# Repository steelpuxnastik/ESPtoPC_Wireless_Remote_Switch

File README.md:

# ESPtoPC Wireless Remote Switch

Remote power-on / reset / force-shutdown for a desktop PC over WiFi, using an ESP-01 wired to the motherboard's front-panel header, plus an OpenWrt app (LuCI page + CLI) to manage one or more of these boards.

Built for the case where a PC needs to be turned on remotely even after a power outage — before the OS is up, before Wake-on-LAN is usable — by literally pressing the physical power button in software.

## Repo layout

```
├── esptopc_poweron_remote_pcb/
│   ├── esptopc_poweron_remote_pcb.kicad_pro   KiCad project
│   ├── esptopc_poweron_remote_pcb.kicad_pcb   Board layout
│   ├── esptopc_poweron_remote_pcb.kicad_sch   Schematic
│   └── esptopc_poweron_remote_pcb.kicad_prl   KiCad local project settings
├── esptopc_poweron_remote/
│   └── esptopc_poweron_remote.ino             ESP8266 (ESP-01) firmware
└── openwrt_program/
    └── deploy.sh                              One-shot installer for the OpenWrt side:
                                               LuCI app + CLI tool + handshake listener
```

## How it fits together

```
[ESP-01 board]  --HTTP-->  [OpenWrt router]  <--LuCI/SSH--  [you]
   |    ^                     |
   |    |                     |-- LuCI page: device list, status, buttons
   |    `-- commands sent      -- CLI (`esptopcrsw`): menu + one-liners
   |        by OpenWrt         -- receives handshake/heartbeat from ESP
   `-- wired to PC's
       PWR_SW / RESET_SW
       header + reads the
       power-LED line
```

- The ESP-01 runs its own tiny HTTP server (power on / force off / reset / status) and also announces itself to the router (MAC + a fixed identifying string) so it shows up in LuCI ready to be named and saved.
- The OpenWrt side is the "brain": it tracks device state, decides which buttons make sense to show (e.g. no point offering "Reset" on a PC that's already off), and is what you actually interact with — LuCI in a browser, or `esptopcrsw` over SSH.

## Hardware (KiCad project)

Open `esptopc_poweron_remote_pcb.kicad_pro` in KiCad. The board:

- Regulates the PC's 5V standby rail down to 3.3V (AMS1117-3.3) to power the ESP-01;
- Uses two small MOSFET pairs (PMOS+NMOS per line) so the ESP's GPIO1 (TX) and GPIO3 (RX) can pull the motherboard's **PWR_SW** and **RESET_SW** header pins low, exactly like pressing the physical buttons;
- Reads the motherboard's power-LED line through a third MOSFET into GPIO2, to sense whether the PC is currently on (active-low: LOW = on);
- Leaves GPIO0 completely unused/unconnected on purpose, to avoid accidentally dropping into the bootloader.

### List of required components for board assembly

| Reference | Qty | Value | Footprint | Datasheet |
| :--- | :--- | :--- | :--- | :--- |
| **C1** | 1 | 22uF | Capacitor_Tantalum_SMD:CP_EIA-3528-21_Kemet-B_HandSolder | |
| **C2** | 1 | 150uF | Capacitor_Tantalum_SMD:CP_EIA-6032-28_Kemet-C_HandSolder | |
| **C3** | 1 | 100nF | Capacitor_SMD:C_1206_3216Metric_Pad1.33x1.80mm_HandSolder | |
| **C4** | 1 | 1uF | Capacitor_SMD:C_0805_2012Metric_Pad1.18x1.45mm_HandSolder | |
| **J1** | 1 | Conn_01x05_Pin | Connector_PinHeader_2.54mm:PinHeader_1x05_P2.54mm_Vertical | |
| **Q1, Q3** | 2 | IRLML6402 | Package_TO_SOT_SMD:SOT-23_Handsoldering | |
| **Q2, Q4, Q5** | 3 | IRLML2502 | Package_TO_SOT_SMD:SOT-23_Handsoldering | |
| **R1, R2, R3, R4, R5, R6, R8, R9** | 8 | 10k | Resistor_SMD:R_1206_3216Metric_Pad1.30x1.75mm_HandSolder | |
| **R7** | 1 | 1k | Resistor_SMD:R_0805_2012Metric | |
| **U1** | 1 | AMS1117-3.3 (fixed 3.3V version) | Package_TO_SOT_SMD:SOT-223-3_TabPin2 | [Datasheet](http://www.advanced-monolithic.com/pdf/ds1117.pdf) |
| **U2** | 1 | ESP-01 | RF_Module:ESP-01 | [Datasheet](https://aithinker-static.oss-cn-shenzhen.aliyuncs.com/docs/_media_old/esp-01_product_specification_en.pdf) |

## Connection to PC

Connector `J1` (5-pin) goes to the motherboard. Pinout as drawn in the schematic:

| J1 pin | Signal | Connect to |
| :--- | :--- | :--- |
| 1 | LED+ | Power-LED (PLED+) pin of the motherboard's front-panel header |
| 2 | RESET | Signal pin of the RESET_SW header (not the ground pin) |
| 3 | POWER | Signal pin of the PWR_SW header (not the ground pin) |
| 4 | GND | Ground |
| 5 | +5V | +5V standby — must stay powered while the PC is off |

Front-panel header pinouts differ between motherboards, so check the manual of yours before connecting.

## Firmware (`esptopc_poweron_remote.ino`)

Flash with the Arduino IDE (ESP8266 core) via a USB-serial adapter. **TX/RX are used to drive the buttons**, so there's no Serial debug output. Flashing needs the special adapter, so you need to disconnect ESP-01 from the board first.

Before flashing, edit near the top of the file:

- `WIFI_SSID` / `WIFI_PASS` — your network;
- `DEVICE_PASSWORD` — a shared password string. The board sends it to the router in the handshake (so the router knows it's one of yours), and it is also the seed of the per-device command key (see **Security** below). It must match `esptopcrsw.settings.password` on the router; the default `poweron-esp01` is already the same on both sides, so you don't have to change it;
- `POWER_SHORT_MS = 300` - A short press of the Power button. The configured press duration setting should work in most cases;
- `POWER_SOFTOFF_MS  = 4500` - Hold the Power button for the BIOS "soft-off delay" (e.g. Gigabyte: *Soft-Off by PWR-BTN = Delay 4 Sec*: a short press only suspends the PC, holding the button for 4+ seconds turns it off). It is only a fallback: the router normally sends its own time, see **Button press times** below;
- `POWER_FORCEOFF_MS = 5000` - Long-press the Power button to force the system unit to shut down. The required duration of the press can vary significantly between different computers; if it does not work, you will need to experiment to find the right timing;
- `RESET_SHORT_MS = 300` - A short press of the Reset button. The configured press duration setting should work in most cases;
- `WIFI_RETRY_MS = 30000` - While the board is not connected to WiFi (for example, the router is still booting after a power outage), it retries the connection every 30 seconds, forever;
- `HANDSHAKE_INTERVAL_MS = 10000` - Once the board is on WiFi, until the OpenWrt app acknowledges it, it announces itself every 10 seconds;
- `HEARTBEAT_INTERVAL_MS = 90000` - After the acknowledgment the board repeats the announcement every 90 seconds to show it is still alive.

How the heartbeat is used: the router stores the time of the last announcement in RAM, continuously, whether or not anyone has the LuCI page open. A device is shown as Offline if nothing was heard from it for 5 minutes. The PC's on/off state does not come from the heartbeat — it is read live from the board when you open the page (and every 15 seconds while the page stays open). The only case with a wait is right after the router itself reboots: its RAM is empty, so a device shows as Offline until its next announcement (up to the heartbeat interval). A shorter `HEARTBEAT_INTERVAL_MS` shortens that wait.

The board finds the router automatically (`WiFi.gatewayIP()`, no IP to hardcode) and keeps retrying forever, so boot order after a power outage doesn't matter.

HTTP endpoints the board exposes (all require `?key=...`, see below):

| Endpoint         | Effect                        |
|-------------------|-------------------------------|
| `GET /power/on[?ms=N]`   | Short press of the power button (default `POWER_SHORT_MS`; limited to 100–2000) |
| `GET /power/hold[?ms=N]` | Hold the power button (default `POWER_SOFTOFF_MS`; limited to 500–10000) |
| `GET /power/off[?ms=N]`  | Long press, force shutdown (default `POWER_FORCEOFF_MS`; limited to 1000–15000) |
| `GET /reset[?ms=N]`      | Press of the reset button (default `RESET_SHORT_MS`; limited to 100–2000) |
| `GET /status`     | `{"pc_status":"on"\|"off"}`   |

All permission logic (e.g. "don't offer Reset while the PC is off") lives on the OpenWrt side, not in the firmware — the board just does what it's told and reports state.

## OpenWrt app (`deploy.sh`)

Self-contained installer — no package manager involved, just copies files to their real system paths and (re)starts the relevant services. Built against OpenWrt 25.x (APK-based, modern JSON-based LuCI menu/ACL — the classic Lua-controller style LuCI apps won't work the same way on this version).

### Install

On Windows, in CMD, I use this to copy `deploy.sh` to the router:
```CMD
scp X:\way\to\your\deploy.sh root@<router-ip>:/root/
```
After this, connect to the router over SSH and install the app:
```sh
ssh root@<router-ip>
sh deploy.sh
```

Re-running `deploy.sh` after an update is safe — it won't wipe devices you've already added (`/etc/config/esptopcrsw` is only created if missing).

What it sets up:
- LuCI page under **Services → ESPtoPC Wireless Remote Switch**: device table with live status (On / Off / Offline), buttons that adapt to state, add-device picker (from the router's DHCP client list or typed by hand), and a banner for boards that announced themselves but aren't saved yet (it has a Dismiss button; a dismissed board shows up again when it announces itself next time). **Initial setup and adding devices is carried out only in LuCI's ESPtoPC Wireless Remote Switch program page**;
- `esptopcrsw` CLI (see below; use it only after the setup in LuCI is done and checked);
- A second `uhttpd` instance on port 8090 that receives the handshake/heartbeat from ESP boards;
- `rpcd`/`ubus` backend (`/usr/libexec/rpcd/esptopcrsw`) that both the LuCI page and the CLI talk to.

### CLI

> **Important:**
> Use the CLI only after the program is set up in LuCI and you have checked that everything works as you expect: devices are added, the status is shown correctly, and the press times (the **Settings** button of each device) fit your PC. The CLI does not add devices or change settings, it only sends commands using what is configured in LuCI.

```sh
esptopcrsw                     # interactive menu, a convenient alternative to manual command entry
esptopcrsw list                # table of devices + status
esptopcrsw poweron <name>      # power on (or sleep, if already on)
esptopcrsw softoff <name>      # soft-off: hold Power for the BIOS delay (see below; `hold` is an alias)
esptopcrsw off <name>          # force power off (long hold)
esptopcrsw reset <name>
esptopcrsw check <name>        # check/restore connection
esptopcrsw help                # show help (list of commands and hints)
esptopcrsw lang [en|ru|uk]     # interface language (remembered)
```

Any of `poweron` / `softoff` / `off` / `reset` asks for a one-letter confirmation first (`y/N`) naming the device and the action, so a stray keypress can't send a command to the wrong PC. If a device looks offline when you run a command, the CLI tries to reconnect first and reports what happened, instead of failing silently.

### Button press times and Soft-Off

**Soft-Off is optional and aimed at Gigabyte boards.** Some Gigabyte BIOSes have *Soft-Off by PWR-BTN* (*Instant-Off* / *Delay 4 Sec*). With *Delay 4 Sec* a short press only suspends the PC, and a press held for 4 seconds shuts it down normally. If your board has no such option, you only need **Off / Sleep** and **Force Off**. The same action also covers any other case where the PC expects a Power press of a specific length: set that length as the hold time.

Power button actions, from shortest to longest: **Off / Sleep** (short press, what the PC does depends on its power settings), **Soft-Off (X s)** (hold for the BIOS soft-off delay), **Force Off** (long hold, `POWER_FORCEOFF_MS`), and **Reset**.

If a short press does not shut the PC down (on Gigabyte boards the BIOS option *Soft-Off by PWR-BTN* set to *Delay 4 Sec* makes a short press only suspend it), use **Soft-Off (X s)**. `X` is set with the **Settings** button in LuCI (in seconds) or on the router, no reflashing needed:

All press times are set per device in LuCI, in seconds, no reflashing needed: the **Settings** button in the device's *Manage* column (an empty field means the built-in value). The same options can be set with `uci` in the device section:

```sh
uci set esptopcrsw.@device[0].soft_off_ms='6000'    # the first device, ms
uci commit esptopcrsw
```

| Option | Action | Default | Allowed, ms |
|---|---|---|---|
| `power_short_ms` | Off / Sleep (short Power press) | 300 | 100–2000 |
| `soft_off_ms` | Soft-Off (Power hold for the BIOS delay) | 4500 | 500–10000 |
| `force_off_ms` | Force Off (long Power hold) | 5000 | 1000–15000 |
| `reset_ms` | Reset | 300 | 100–2000 |

The Soft-Off button label in LuCI and in the CLI shows the current value for that device. Unlike the short press, this button is not blocked in the first minute after power-on.

### Security

There's no login/password on the ESP's HTTP server itself — instead:

- **Handshake** (ESP → router): the board POSTs its MAC and `DEVICE_PASSWORD` to the router on boot/periodically, so the router knows it's genuinely this project's firmware announcing itself. It only filters out random devices, and it is sent in plain text.
- **Commands** (router → ESP): every `/power/on`, `/power/hold`, `/power/off`, `/reset`, `/status` call requires `?key=<12-hex-chars>`, computed as `md5(MAC:DEVICE_PASSWORD)` truncated to 12 characters — the same formula on both sides, so no separate secret needs to be distributed or synced per board. Each board gets a different key because its MAC is different. This stops a stray browser tab pointed at the board's IP from doing anything. It is **not** protection against someone who deliberately reads this repo (the formula and the default password are public), and it's **not encryption**: the key is part of the URL, so anyone sniffing the WiFi traffic can read it in plain text. Good enough for "don't let someone on the LAN poke it by accident", not meant to survive a hostile network. If you want more than the default, set your own string in `DEVICE_PASSWORD` in the firmware and in `uci set esptopcrsw.settings.password='...'` on the router.

## Known rough edges

- The rpcd/JS/LuCI layer was written against documented conventions for modern OpenWrt (menu.d/acl.d JSON, JS views over ubus) but hasn't been exhaustively tested beyond this one setup — if something in LuCI breaks after an OpenWrt upgrade, that's the first place to look.
- `busybox tr` on some builds doesn't support POSIX character classes (`[:lower:]`/`[:upper:]`) — the scripts here use explicit ranges (`a-z`/`A-Z`) everywhere for that reason; keep that in mind if you extend them.
- MAC addresses are stored/compared uppercase throughout, to avoid the same device getting registered twice under different casing.

## To-Do-List
- PCB variant based on ESP12E, that will be simpler in some areas in terms of harnessing components, plus it's protected by default from all the side effects that previously had to be addressed by monitoring the input from the PC's operating status pin. 
- Create a simplified default pass-through connection for all connectors, plus the ability to connect to the power supply with just one 5Vsb wire.

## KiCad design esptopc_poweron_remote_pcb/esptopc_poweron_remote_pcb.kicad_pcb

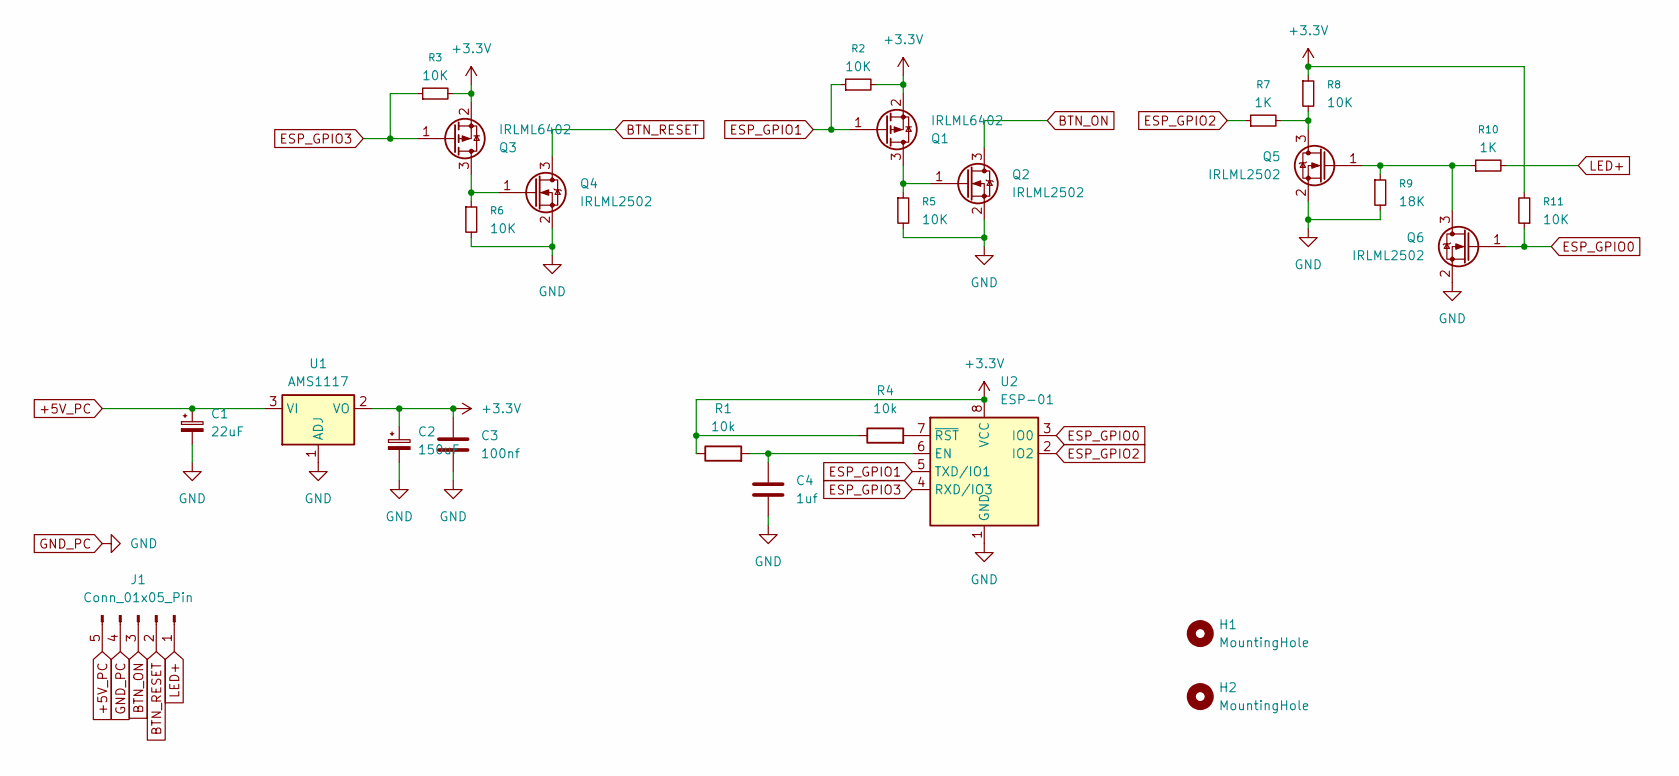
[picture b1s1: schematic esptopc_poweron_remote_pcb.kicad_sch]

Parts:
C1: 22uF; CP_EIA-3528-21_Kemet-B_HandSolder
C2: 150uF; CP_EIA-6032-28_Kemet-C_HandSolder
C3: 100nf; C_1206_3216Metric_Pad1.33x1.80mm_HandSolder
C4: 1uf; C_0805_2012Metric_Pad1.18x1.45mm_HandSolder
H1, H2: MountingHole; MountingHole_3.2mm_M3
J1: Conn_01x05_Pin; PinHeader_1x05_P2.54mm_Vertical
Q1, Q3: IRLML6402; SOT-23_Handsoldering
Q2, Q4, Q5, Q6: IRLML2502; SOT-23_Handsoldering
R1, R4: 10k; R_1206_3216Metric_Pad1.30x1.75mm_HandSolder
R2, R3, R5, R6, R8, R11: 10K; R_1206_3216Metric_Pad1.30x1.75mm_HandSolder
R7: 1K; R_0805_2012Metric
R9: 18K; R_0805_2012Metric_Pad1.20x1.40mm_HandSolder
R10: 1K; R_0805_2012Metric_Pad1.20x1.40mm_HandSolder
U1: AMS1117; SOT-223-3_TabPin2
U2: ESP-01

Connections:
+3.3V: C2.1, C3.1, Q1.2 (S), Q3.2 (S), R1.1, R2.2, R3.2, R4.1, R8.1, R11.2, U1.2 (VO), U2.8 (VCC)
+5V_PC: C1.1, J1.5, U1.3 (VI)
BTN_ON: J1.3, Q2.3 (D)
BTN_RESET: J1.2, Q4.3 (D)
ESP_GPIO0: Q6.1 (G), R11.1, U2.3 (IO0)
ESP_GPIO1: Q1.1 (G), R2.1, U2.5 (TXD/IO1)
ESP_GPIO2: R7.1, U2.2 (IO2)
ESP_GPIO3: Q3.1 (G), R3.1, U2.4 (RXD/IO3)
GND_PC: C1.2, C2.2, C3.2, C4.2, J1.4, Q2.2 (S), Q4.2 (S), Q5.2 (S), Q6.2 (S), R5.2, R6.2, R9.2, U1.1 (ADJ), U2.1 (GND)
LED+: J1.1, R10.2
unnamed: Q1.3 (D), Q2.1 (G), R5.1
unnamed: Q3.3 (D), Q4.1 (G), R6.1
unnamed: Q5.3 (D), R7.2, R8.2
unnamed: Q5.1 (G), Q6.3 (D), R9.1, R10.1
unnamed: C4.1, R1.2, U2.6 (EN)
unnamed: R4.2, U2.7 (~RST)

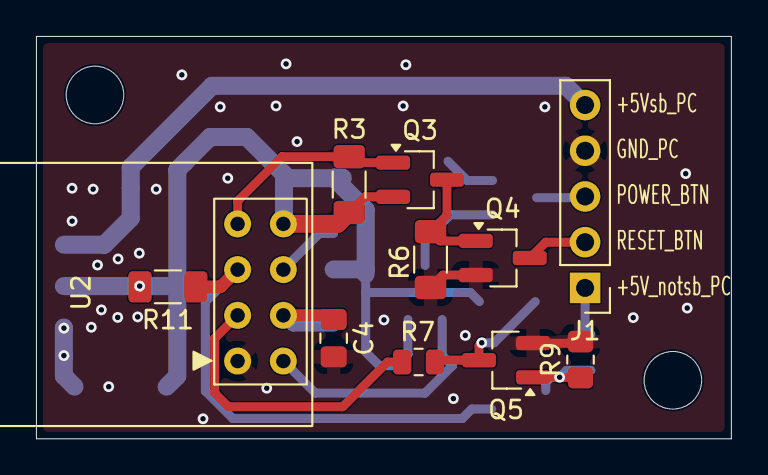
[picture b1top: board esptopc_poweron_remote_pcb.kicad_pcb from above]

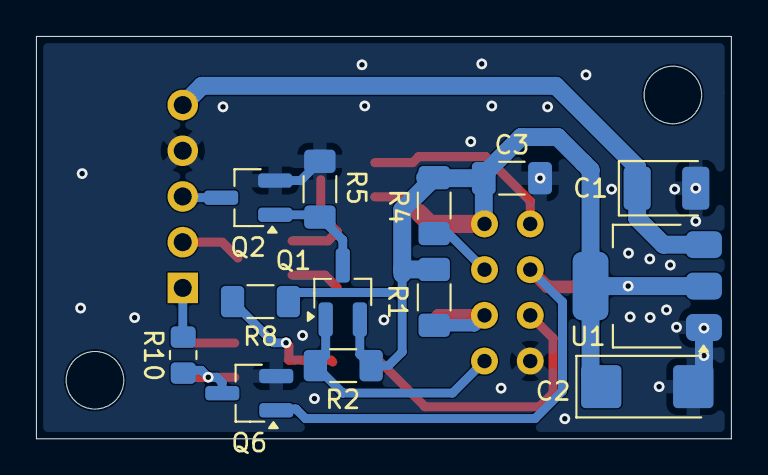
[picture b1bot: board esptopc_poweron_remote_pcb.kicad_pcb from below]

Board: 2 copper layers, 38.6 x 22.4 mm, 26 parts (13 on the bottom side), 16 nets.
